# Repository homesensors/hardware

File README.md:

# homesensors / hardware

Open-hardware KiCad projects for the
[`homesensors`](https://github.com/homesensors/sensorkit) DIY
smart-home sensor kit. Multiple PCBs live here as peer sub-projects
under their own subfolders; each board is a self-contained KiCad
project with its own README, BOM, and revision history.

## Board family

| Subfolder | Status | What it is |
|---|---|---|
| [`door_sensor/`](door_sensor/) | **Rev A fabricated, Rev B at fab** | Single-purpose BLE door sensor (STM32WB09 + TCS40DPR Hall + CR2032). The first board in the family; what the rest of `homesensors` was originally designed around. |
| `carrier_ble/` | *Planned* | Modular-architecture carrier board with on-board STM32WB09 BLE radio + power input + mikroBUS extension socket. Per [`docs/modular-spec.md`](https://github.com/homesensors/sensorkit/blob/main/docs/modular-spec.md). |
| `carrier_wifi/` | *Future* | ESP32-based carrier board, same connector contract. |
| `carrier_zigbee/` | *Future* | EFR32MG24-based carrier board. |
| `carrier_lora/` | *Future* | STM32WLE5-based carrier board. |
| `extension_door/` | *Planned* | Door-contact sensor as a modular extension (replaces the standalone `door_sensor/` once the modular line stabilises). |
| `extension_temp_humidity/` | *Future* | Temperature + humidity I2C extension. |
| *(more extensions)* | *Future* | Motion, leak, fire, power, audio, vibration… see modular-spec §5.4 ID table. |

## Repository layout

```
hardware/
├── README.md                ← this file
├── LICENSE                  ← CERN-OHL-P-2.0, applies to every board
├── .gitignore               ← KiCad cruft (backups, fp-info-cache, *.kicad_prl)
├── libraries/               ← shared symbol/footprint libs (added when there's something to share)
│   ├── homesensors.kicad_sym   (planned)
│   └── homesensors.pretty/     (planned)
└── <board>/                 ← per-board KiCad project (one subfolder per PCB)
    ├── README.md            ← board-specific docs + revision history
    ├── <name>.kicad_pro
    ├── <name>.kicad_sch
    ├── <name>.kicad_pcb
    ├── <name>.kicad_dru     ← design rules
    ├── <name>.csv           ← BOM export
    ├── fab/                 ← (when generated) Gerbers + drill + P&P
    ├── bom/                 ← (when generated) sourcing-ready BOM with LCSC PNs
    └── 3d/                  ← (when generated) board-level renders
```

Each board's project lives in its own subfolder so that KiCad's
`<project>-backups/` dir stays adjacent to the project that produced
it, and so that `fab/` outputs from one board don't mix with another.

## Versioning

Tags are namespaced by board: `door_sensor-rev-a`, `carrier_ble-rev-a`,
etc. Each board carries its own revision sequence and is fabbed
independently.

For backward-compatibility with the early period when `hardware/` had
only the door sensor at its root, the unscoped tags `pcb-rev-a` and
`pcb-rev-b` are preserved as aliases pointing at the same commits as
`door_sensor-rev-a` and `door_sensor-rev-b` respectively. Don't add
unscoped tags going forward.

## License

CERN-OHL-P-2.0 — see [LICENSE](LICENSE). Permissive open hardware:
fork the designs, fab them, sell physical units, no copyleft strings.
Just preserve the licence + notices.

## Related repos

- [`homesensors/sensorkit`](https://github.com/homesensors/sensorkit) — umbrella docs, protocol spec, modular architecture spec, image gallery.
- [`homesensors/firmware`](https://github.com/homesensors/firmware) — MCU firmware (currently for `door_sensor`; modular framework planned).
- [`homesensors/homeassist`](https://github.com/homesensors/homeassist) — Home Assistant add-on (Tier 1.5 ACK daemon).

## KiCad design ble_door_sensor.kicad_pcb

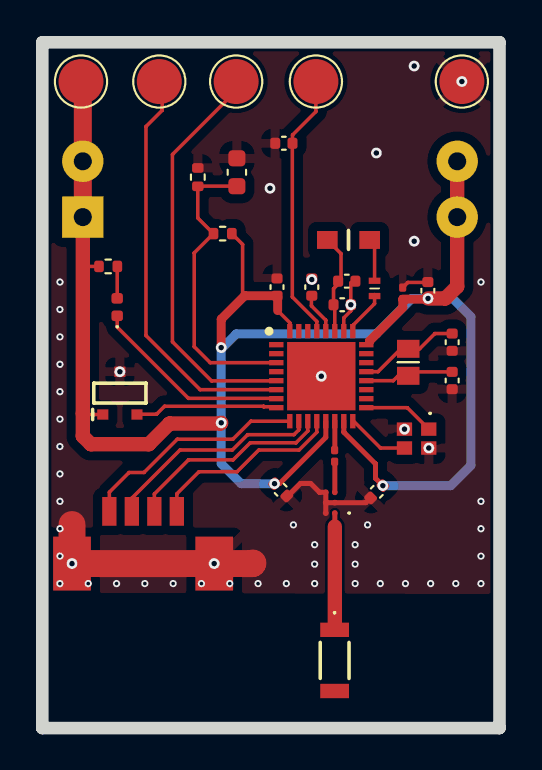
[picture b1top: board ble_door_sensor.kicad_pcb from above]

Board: 2 copper layers, 25.4 x 38.1 mm, 32 parts (1 on the bottom side), 24 nets.

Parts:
ANT1: 2450AT18A0100001E
BT1: CR2032; BATHLD001THM
C1: 20pF; C_0201_0603Metric
C2, C3: 10pF; C_0402_1005Metric
C4, C8, C9: 1uF; C_0402_1005Metric
C5: 100nF; C_0201_0603Metric
C6, C11: 4.7uF; C_0402_1005Metric
C7: 0.22uF; C_0402_1005Metric
C10: 100nF; C_0402_1005Metric
C12: 0.1uF; C_0402_1005Metric
C13: 0.1uF; C_0603_1608Metric
D1: LED; LED_0402_1005Metric
IC1: MLPF-NRG-01D3; CSPG_2025
IC2: TCS40DPR,LF; SOTFL95P240X88-3N
J1: Conn_01x04_Pin; JST_MX_4P-1_25
L1: 22nH; LQG15WH0N7B02D
L2: 10uH; LQM21DN220N00L
R1: 510; R_0402_1005Metric
R2, R3: 1M; R_0402_1005Metric
TP1: SWDIO; TestPoint_Pad_D2.5mm
TP2: SWCLK; TestPoint_Pad_D2.5mm
TP3: VCC; TestPoint_Pad_D2.5mm
TP4: nRST; TestPoint_Pad_D2.5mm
TP5: GND; TestPoint_Pad_D2.5mm
U1: STM32WB09KEVx; QFN50P500X500X100-33N-D
Y1: NX2016SA-32M-EXS00A-CS06465; NX2016SA32MEXS00ACS06465
Y2: 32.768KHz; NX2012SA32768KSTDMUB1

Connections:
+3V3: BT1.1 (+), BT1.2 (-), BT1.3, BT1.4, C4.2, C5.1, C6.1, C8.2, C9.2, IC2.1 (VCC), R1.1, R2.1, TP3.1, U1.13 (VDD), U1.15 (VDDRF), U1.24 (VDDSD), U1.32 (VDD)
/SWCLK: TP2.1, U1.5 (PA3)
/SWDIO: TP1.1, U1.6 (PA2)
GND: BT1.5, C2.2, C3.2, C4.1, C5.2, C6.2, C7.1, C8.1, C9.1, C10.2, C11.2, C12.2, C13.2, IC1.A2 (GND4), IC1.B1 (GND3), IC1.B2 (GND2), IC1.B3 (GND1), IC2.3 (GND), J1.4, R3.2, TP5.1, U1.26 (VSSSD), U1.33, Y1.2 (GND_1), Y1.4 (GND_2)
unnamed: ANT1.1 (FEED), IC1.A1 (OUT)
unnamed: D1.2 (A), R1.2
unnamed: D1.1 (K), U1.7 (PA1)
unnamed: C1.2, IC1.A3 (IN)
unnamed: IC2.2 (VOUT), U1.8 (PA0)
unnamed: J1.1, U1.12 (PA11)
unnamed: J1.2, U1.11 (PA10)
unnamed: J1.3, U1.10 (PA9)
unnamed: J1.4, U1.9 (PA8)
unnamed: L1.1, L2.2
unnamed: U1.17 (OSCIN), Y1.1 (CRYSTAL_1)
unnamed: U1.16 (OSCOUT), Y1.3 (CRYSTAL_2)
unnamed: C13.1, R2.2, R3.1, U1.3 (PB1)
unnamed: C2.1, U1.21 (PB12), Y2.2
unnamed: C3.1, U1.20 (PB13), Y2.1
unnamed: C1.1, U1.14 (RF1)
unnamed: C12.1, TP4.1, U1.29 (RSTN)
unnamed: C7.2, U1.28 (VDDA_VCAP)
unnamed: C10.1, C11.1, L2.1, U1.27 (VFBSD)
unnamed: L1.2, U1.25 (VLXSD)
